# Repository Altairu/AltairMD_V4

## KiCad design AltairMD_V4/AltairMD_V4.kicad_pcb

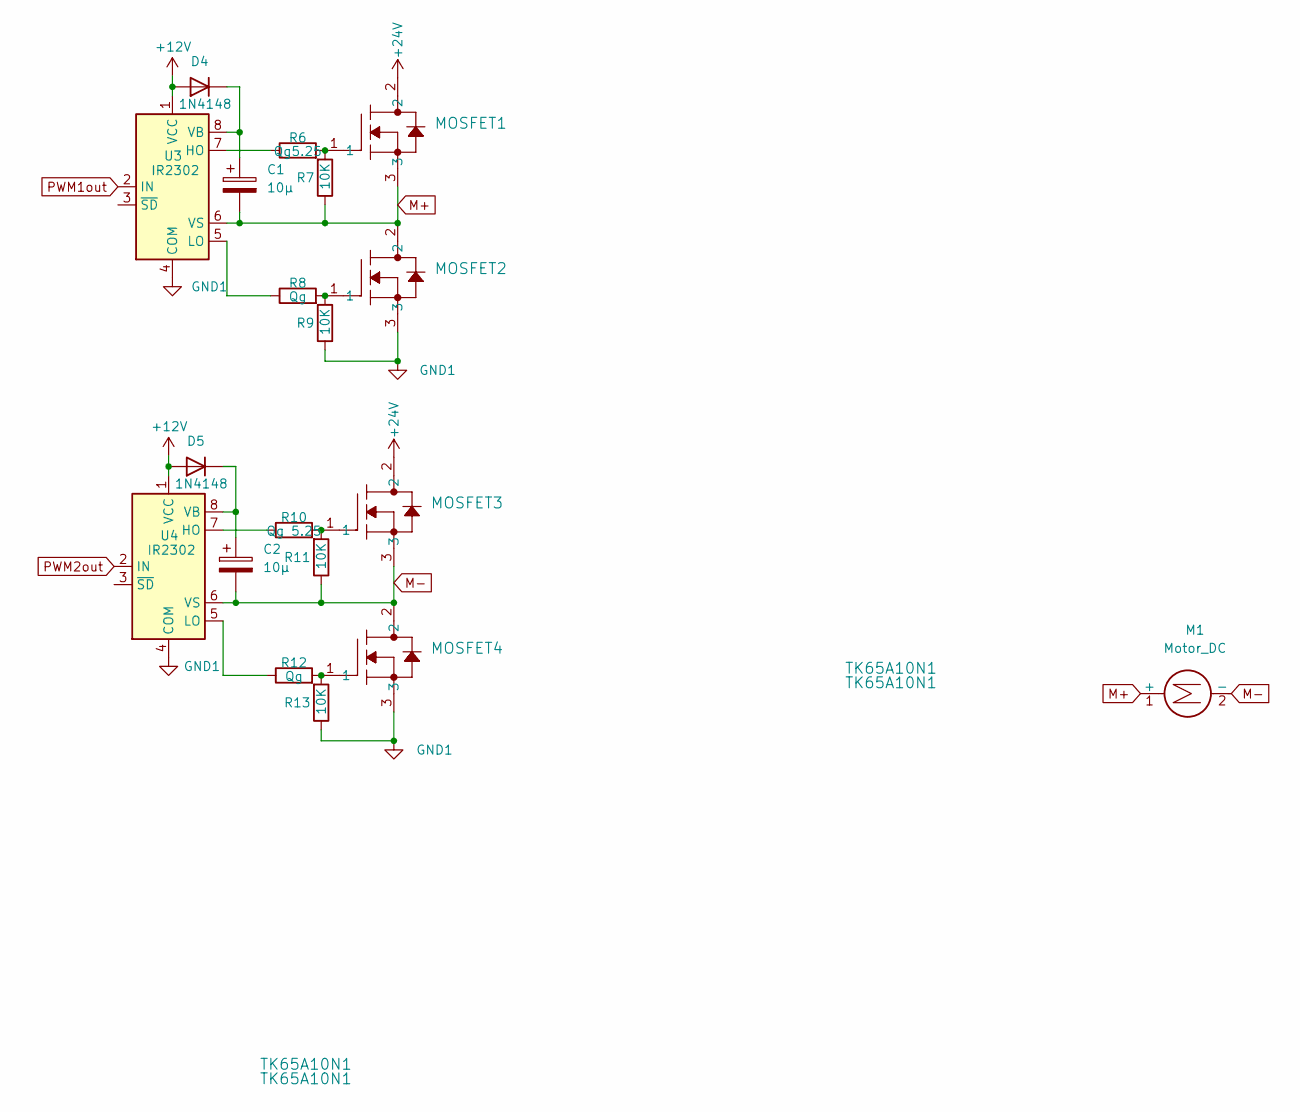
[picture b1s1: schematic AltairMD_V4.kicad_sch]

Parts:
C1, C2: 10μ; CP_Radial_D5.0mm_P2.00mm
D4, D5: 1N4148; D_DO-35_SOD27_P10.16mm_Horizontal
M1: Motor_DC
MOSFET1, MOSFET2, MOSFET3, MOSFET4: TK65A10N1; TO-220-3_Horizontal_TabDown
R6: Qg5.25; R_Axial_DIN0207_L6.3mm_D2.5mm_P10.16mm_Horizontal
R7, R9, R11, R13: 10K; R_Axial_DIN0207_L6.3mm_D2.5mm_P10.16mm_Horizontal
R8, R12: Qg; R_Axial_DIN0207_L6.3mm_D2.5mm_P10.16mm_Horizontal
R10: Qg 5.25; R_Axial_DIN0207_L6.3mm_D2.5mm_P10.16mm_Horizontal
U3, U4: IR2302; DIP-8_W7.62mm

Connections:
+12V: D4.2 (A), D5.2 (A), U3.1 (VCC), U4.1 (VCC)
+24V: MOSFET1.2, MOSFET3.2
GND1: MOSFET2.3, MOSFET4.3, R9.1, R13.1, U3.4 (COM), U4.4 (COM)
M+: C1.2, M1.1 (+), MOSFET1.3, MOSFET2.2, R7.1, U3.6 (VS)
M-: C2.2, M1.2 (-), MOSFET3.3, MOSFET4.2, R11.1, U4.6 (VS)
unnamed: C1.1, D4.1 (K), U3.8 (VB)
unnamed: C2.1, D5.1 (K), U4.8 (VB)
unnamed: MOSFET1.1, R6.2, R7.2
unnamed: MOSFET2.1, R8.2, R9.2
unnamed: MOSFET3.1, R10.2, R11.2
unnamed: MOSFET4.1, R12.2, R13.2
unnamed: R6.1, U3.7 (HO)
unnamed: R8.1, U3.5 (LO)
unnamed: R10.1, U4.7 (HO)
unnamed: R12.1, U4.5 (LO)
PWM1out: U3.2 (IN)
PWM2out: U4.2 (IN)

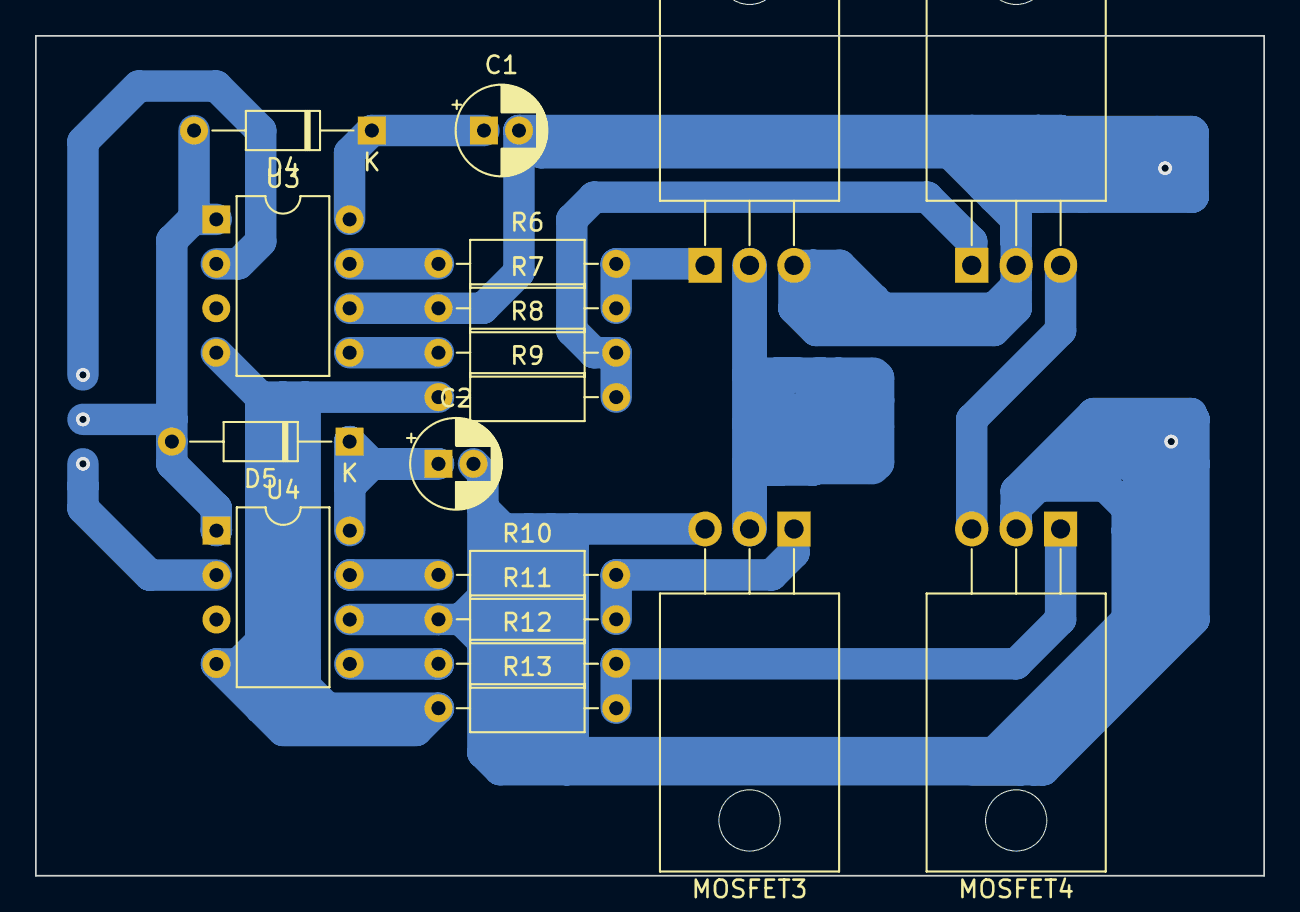
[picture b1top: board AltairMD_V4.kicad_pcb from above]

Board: 2 copper layers, 70.2 x 48.0 mm, 18 parts (0 on the bottom side), 15 nets.
